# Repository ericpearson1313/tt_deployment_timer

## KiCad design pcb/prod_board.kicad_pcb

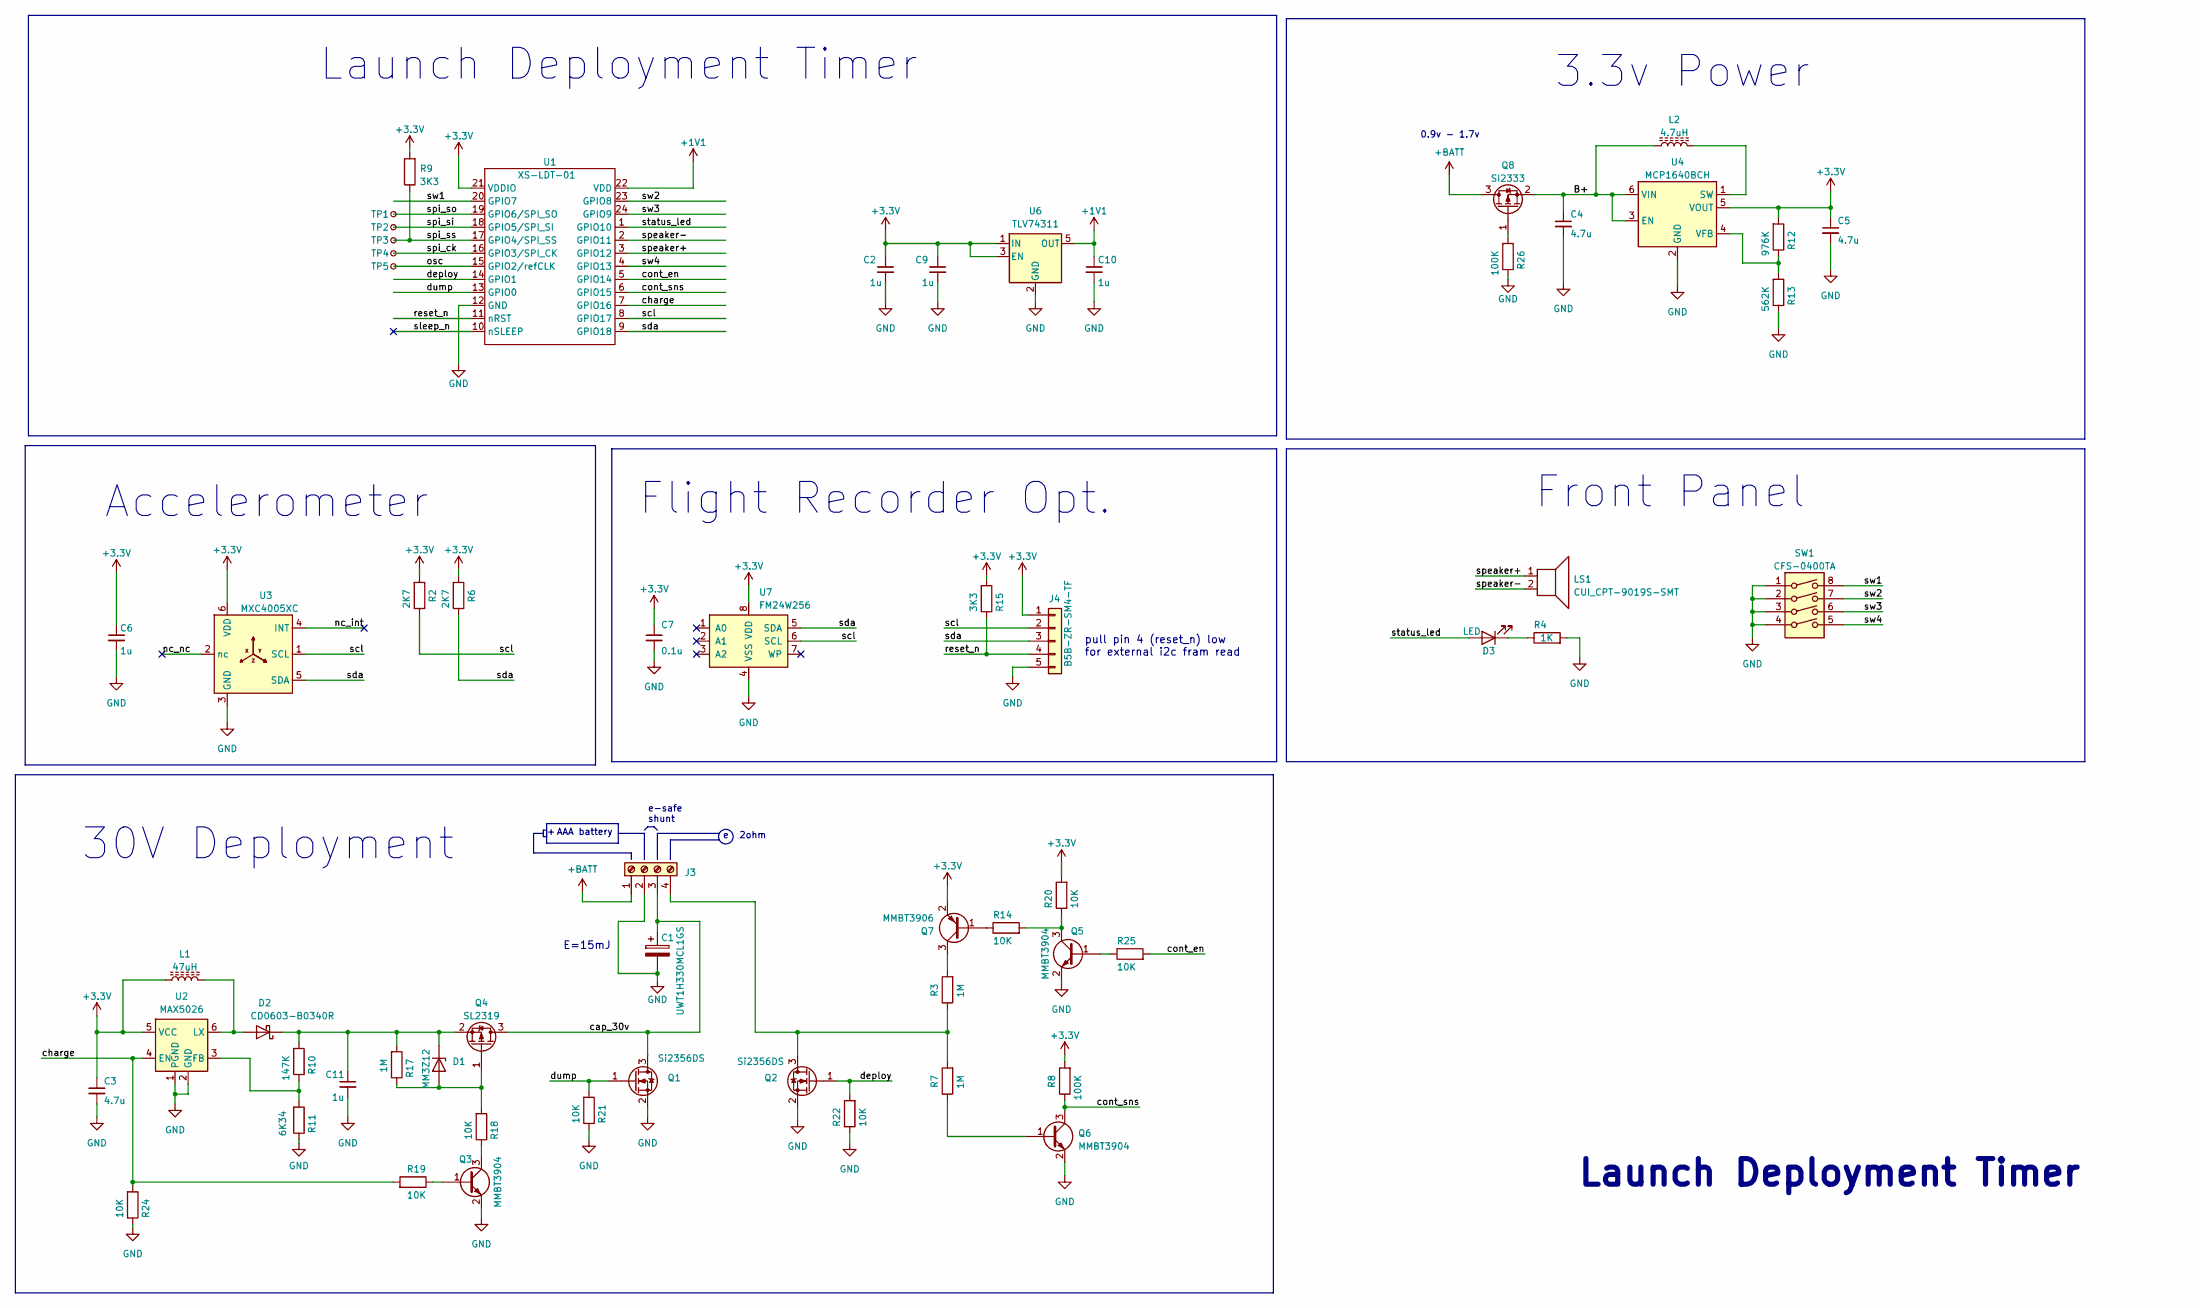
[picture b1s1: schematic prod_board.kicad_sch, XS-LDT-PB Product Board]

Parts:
C1: UWT1H330MCL1GS; CP_Elec_6.3x7.7; LCSC PN C1864193
C2, C6, C9, C10, C11: 1u; C_0603_1608Metric; LCSC PN C15849
C3, C4, C5: 4.7u; C_1206_3216Metric; LCSC PN C29823
C7: 0.1u; C_0603_1608Metric; LCSC PN C14663
D1: MM3Z12; D_SOD-323F; LCSC PN C19077460
D2: CD0603-B0340R; D_0603_1608Metric; LCSC PN C3759853
D3: LED; LED_0603_1608Metric; LCSC PN C2899911
J3: TE_282834-4; TerminalBlock_TE_282834-4_1x04_P2.54mm_Horizontal; LCSC PN C708735
J4: B5B-ZR-SM4-TF; CONN_B5B-ZR-SM4-TF_JST; LCSC PN C265440
L1: 47uH; L_1210_3225Metric; LCSC PN C250235
L2: 4.7uH; L_1210_3225Metric; LCSC PN C117731
LS1: CUI_CPT-9019S-SMT; Buzzer_CUI_CPT-9019S-SMT; LCSC PN C18212234
Q1, Q2: Si2356DS; SOT-23; LCSC PN C5182104
Q3, Q5, Q6: MMBT3904; SOT-23; LCSC PN C7420353
Q4: SL2319; SOT-23; LCSC PN C347478
Q7: MMBT3906; SOT-23; LCSC PN C7420354
Q8: SI2333; SOT-23; LCSC PN C344008
R2, R6: 2K7; R_0603_1608Metric; LCSC PN C13167
R3, R7, R17: 1M; R_0603_1608Metric; LCSC PN C22935
R4: 1K; R_0603_1608Metric; LCSC PN C21190
R8, R26: 100K; R_0603_1608Metric; LCSC PN C25803
R9, R15: 3K3; R_0603_1608Metric; LCSC PN C22978
R10: 147K; R_0603_1608Metric; LCSC PN C2998060
R11: 6K34; R_0603_1608Metric; LCSC PN C23087
R12: 976K; R_0603_1608Metric; LCSC PN C2933270
R13: 562K; R_0603_1608Metric; LCSC PN C2933238
R14, R18, R19, R20, R21, R22, R24, R25: 10K; R_0603_1608Metric; LCSC PN C25804
SW1: CFS-0400TA; SW_DIP_SPSTx04_Slide_6.7x11.72mm_W6.73mm_P2.54mm_LowProfile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; LCSC PN C5774648
TP1, TP2, TP3, TP4, TP5: TestPoint_Small; TestPoint_Pad_D1.0mm
U1: XS-LDT-01; QFN-24-3x3mm
U2: MAX5026; SOT-23-6; LCSC PN C87603
U3: MXC4005XC; MXC4005XC_MEM-M; LCSC PN C404327
U4: MCP1640BCH; SOT-23-6; LCSC PN C478087
U6: TLV74311; SOT-23-5; LCSC PN C485147
U7: FM24W256; SOIC-8_3.9x4.9mm_P1.27mm; LCSC PN C66020

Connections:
+1V1: C10.1, U1.22 (VDD), U6.5 (OUT)
+3.3V: C2.1, C3.1, C5.1, C6.1, C7.1, C9.1, J4.1, L1.1, Q7.2 (E), R2.2, R6.2, R8.2, R9.2, R12.2, R15.2, R20.2, U1.21 (VDDIO), U2.5 (VCC), U3.6 (VDD), U4.5 (VOUT), U6.1 (IN), U6.3 (EN), U7.8 (VDD)
+BATT: J3.1, Q8.3 (D)
/B+: C4.1, L2.1, Q8.2 (S), U4.3 (EN), U4.6 (VIN)
/cap_30v: C1.1, J3.3, Q1.3 (D), Q4.3 (D)
/charge: R19.2, R24.2, U1.7 (GPIO16), U2.4 (EN)
/cont_en: R25.2, U1.5 (GPIO14)
/cont_sns: Q6.3 (C), R8.1, U1.6 (GPIO15)
/deploy: Q2.1 (G), R22.2, U1.14 (GPIO1)
/dump: Q1.1 (G), R21.2, U1.13 (GPIO0)
/nc_int: U3.4 (INT)
/nc_nc: U3.2 (nc)
/osc: TP5.1, U1.15 (GPIO2/refCLK)
/reset_n: J4.4, R15.1, U1.11 (nRST)
/scl: J4.2, R2.1, U1.8 (GPIO17), U3.1 (SCL), U7.6 (SCL)
/sda: J4.3, R6.1, U1.9 (GPIO18), U3.5 (SDA), U7.5 (SDA)
/sleep_n: U1.10 (nSLEEP)
/speaker+: LS1.1, U1.3 (GPIO12)
/speaker-: LS1.2, U1.2 (GPIO11)
/spi_ck: TP4.1, U1.16 (GPIO3/SPI_CK)
/spi_si: TP2.1, U1.18 (GPIO5/SPI_SI)
/spi_so: TP1.1, U1.19 (GPIO6/SPI_SO)
/spi_ss: R9.1, TP3.1, U1.17 (GPIO4/SPI_SS)
/status_led: D3.2 (A), U1.1 (GPIO10)
/sw1: SW1.8, U1.20 (GPIO7)
/sw2: SW1.7, U1.23 (GPIO8)
/sw3: SW1.6, U1.24 (GPIO9)
/sw4: SW1.5, U1.4 (GPIO13)
GND: C1.2, C2.2, C3.2, C4.2, C5.2, C6.2, C7.2, C9.2, C10.2, C11.2, J3.2, J4.5, Q1.2 (S), Q2.2 (S), Q3.2 (E), Q5.2 (E), Q6.2 (E), R4.2, R11.1, R13.1, R21.1, R22.1, R24.1, R26.1, SW1.1, SW1.2, SW1.3, SW1.4, U1.12 (GND), U2.1 (PGND), U2.2 (GND), U3.3 (GND), U4.2 (GND), U6.2 (GND), U7.4 (VSS)
unnamed: D1.2 (A), Q4.1 (G), R17.1, R18.2
unnamed: C11.1, D1.1 (K), D2.1 (K), Q4.2 (S), R10.2, R17.2
unnamed: D2.2 (A), L1.2, U2.6 (LX)
unnamed: D3.1 (K), R4.1
unnamed: J3.4, Q2.3 (D), R3.1, R7.2
unnamed: Q3.1 (B), R19.1
unnamed: Q3.3 (C), R18.1
unnamed: Q5.1 (B), R25.1
unnamed: Q5.3 (C), R14.2, R20.1
unnamed: Q6.1 (B), R7.1
unnamed: Q7.1 (B), R14.1
unnamed: Q7.3 (C), R3.2
unnamed: Q8.1 (G), R26.2
unnamed: R10.1, R11.2, U2.3 (FB)
unnamed: L2.2, U4.1 (SW)
unnamed: R12.1, R13.2, U4.4 (VFB)

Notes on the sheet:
Accelerometer
Front Panel
Launch Deployment Timer
Launch Deployment Timer
2ohm
0.9v - 1.7v
3.3v Power
Flight Recorder Opt.
E=15mJ
pull pin 4 (reset_n) low for external i2c fram read
e-safe shunt
30V Deployment
AAA battery

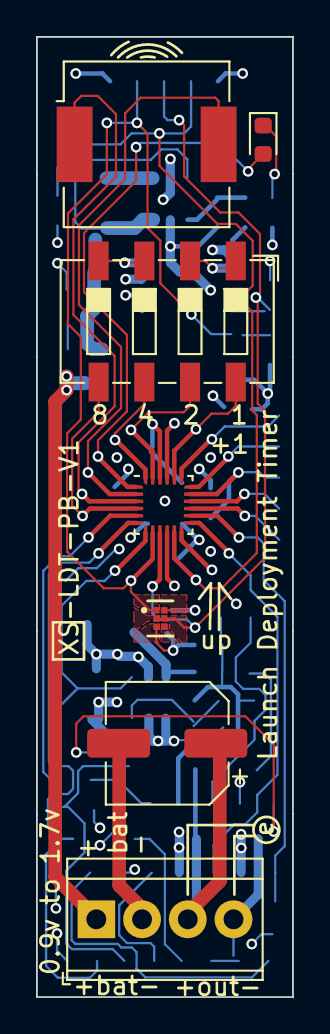
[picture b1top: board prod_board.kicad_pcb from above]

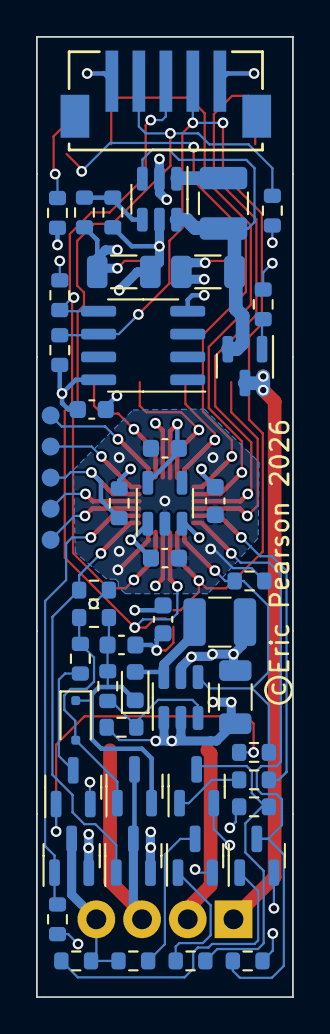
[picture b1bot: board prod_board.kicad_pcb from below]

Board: 4 copper layers, 14.2 x 53.3 mm, 60 parts (53 on the bottom side), 42 nets.

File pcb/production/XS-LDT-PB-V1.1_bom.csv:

Designator,Footprint,Quantity,Value,LCSC Part #
C1,CP_Elec_6.3x7.7,1,UWT1H330MCL1GS,C1864193
"C10, C11, C2, C6, C9",0603,5,1u,C15849
"C3, C4, C5",1206,3,4.7u,C29823
C7,0603,1,0.1u,C14663
D1,D_SOD-323F,1,MM3Z12,C19077460
D2,0603,1,CD0603-B0340R,C3759853
D3,0603,1,LED,C2899911
J3,TerminalBlock_TE_282834-4_1x04_P2.54mm_Horizontal,1,TE_282834-4,C708735
J4,CONN_B5B-ZR-SM4-TF_JST,1,B5B-ZR-SM4-TF,C265440
L1,1210,1,47uH,C250235
L2,1210,1,4.7uH,C117731
LS1,Buzzer_CUI_CPT-9019S-SMT,1,CUI_CPT-9019S-SMT,C18212234
"Q1, Q2",SOT-23,2,Si2356DS,C5182104
"Q3, Q5, Q6",SOT-23,3,MMBT3904,C7420353
Q4,SOT-23,1,SL2319,C347478
Q7,SOT-23,1,MMBT3906,C7420354
Q8,SOT-23,1,SI2333,C344008
R10,0603,1,147K,C2998060
R11,0603,1,6K34,C23087
R12,0603,1,976K,C2933270
R13,0603,1,562K,C2933238
"R14, R18, R19, R20, R21, R22, R24, R25",0603,8,10K,C25804
"R15, R9",0603,2,3K3,C22978
"R17, R3, R7",0603,3,1M,C22935
"R2, R6",0603,2,2K7,C13167
"R26, R8",0603,2,100K,C25803
R4,0603,1,1K,C21190
SW1,SW_DIP_SPSTx04_Slide_6.7x11.72mm_W6.73mm_P2.54mm_LowProfile_JPin,1,CFS-0400TA,C5774648
"TP1, TP2, TP3, TP4, TP5",TestPoint_Pad_D1.0mm,5,TestPoint_Small,
U1,QFN-24-3x3mm,1,XS-LDT-01,
U2,SOT-23-6,1,MAX5026,C87603
U3,MXC4005XC_MEM-M,1,MXC4005XC,C404327
U4,SOT-23-6,1,MCP1640BCH,C478087
U6,SOT-23-5,1,TLV74311,C485147
U7,SOIC-8_3.9x4.9mm_P1.27mm,1,FM24W256,C66020

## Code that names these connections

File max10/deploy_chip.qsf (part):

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set_global_assignment -name POWER_DEFAULT_INPUT_IO_TOGGLE_RATE "12.5 %"
set_location_assignment PIN_33 -to clk_out
set_location_assignment PIN_27 -to clk_in
set_location_assignment PIN_28 -to reset_n
set_location_assignment PIN_86 -to spi8_data_pad[7]
set_location_assignment PIN_84 -to spi8_data_pad[6]
set_location_assignment PIN_79 -to spi8_data_pad[5]
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set_instance_assignment -name IO_STANDARD "3.3-V LVCMOS" -to speaker_n
set_location_assignment PIN_105 -to cont_sense
set_instance_assignment -name IO_STANDARD "3.3-V LVCMOS" -to cont_sense
set_location_assignment PIN_106 -to charge
set_instance_assignment -name IO_STANDARD "3.3-V LVTTL" -to charge
set_location_assignment PIN_102 -to cont_enable
set_location_assignment PIN_66 -to status_led
set_location_assignment PIN_140 -to dump
set_location_assignment PIN_127 -to deploy
set_location_assignment PIN_62 -to sw1
set_location_assignment PIN_135 -to sw2
set_location_assignment PIN_124 -to sw4
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

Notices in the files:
max10/deploy_chip.qsf:
Copyright (C) 2023  Intel Corporation. All rights reserved.
